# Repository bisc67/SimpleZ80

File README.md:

# SimpleZ80
Very simple Z80 SBC. Why? To figure it out.

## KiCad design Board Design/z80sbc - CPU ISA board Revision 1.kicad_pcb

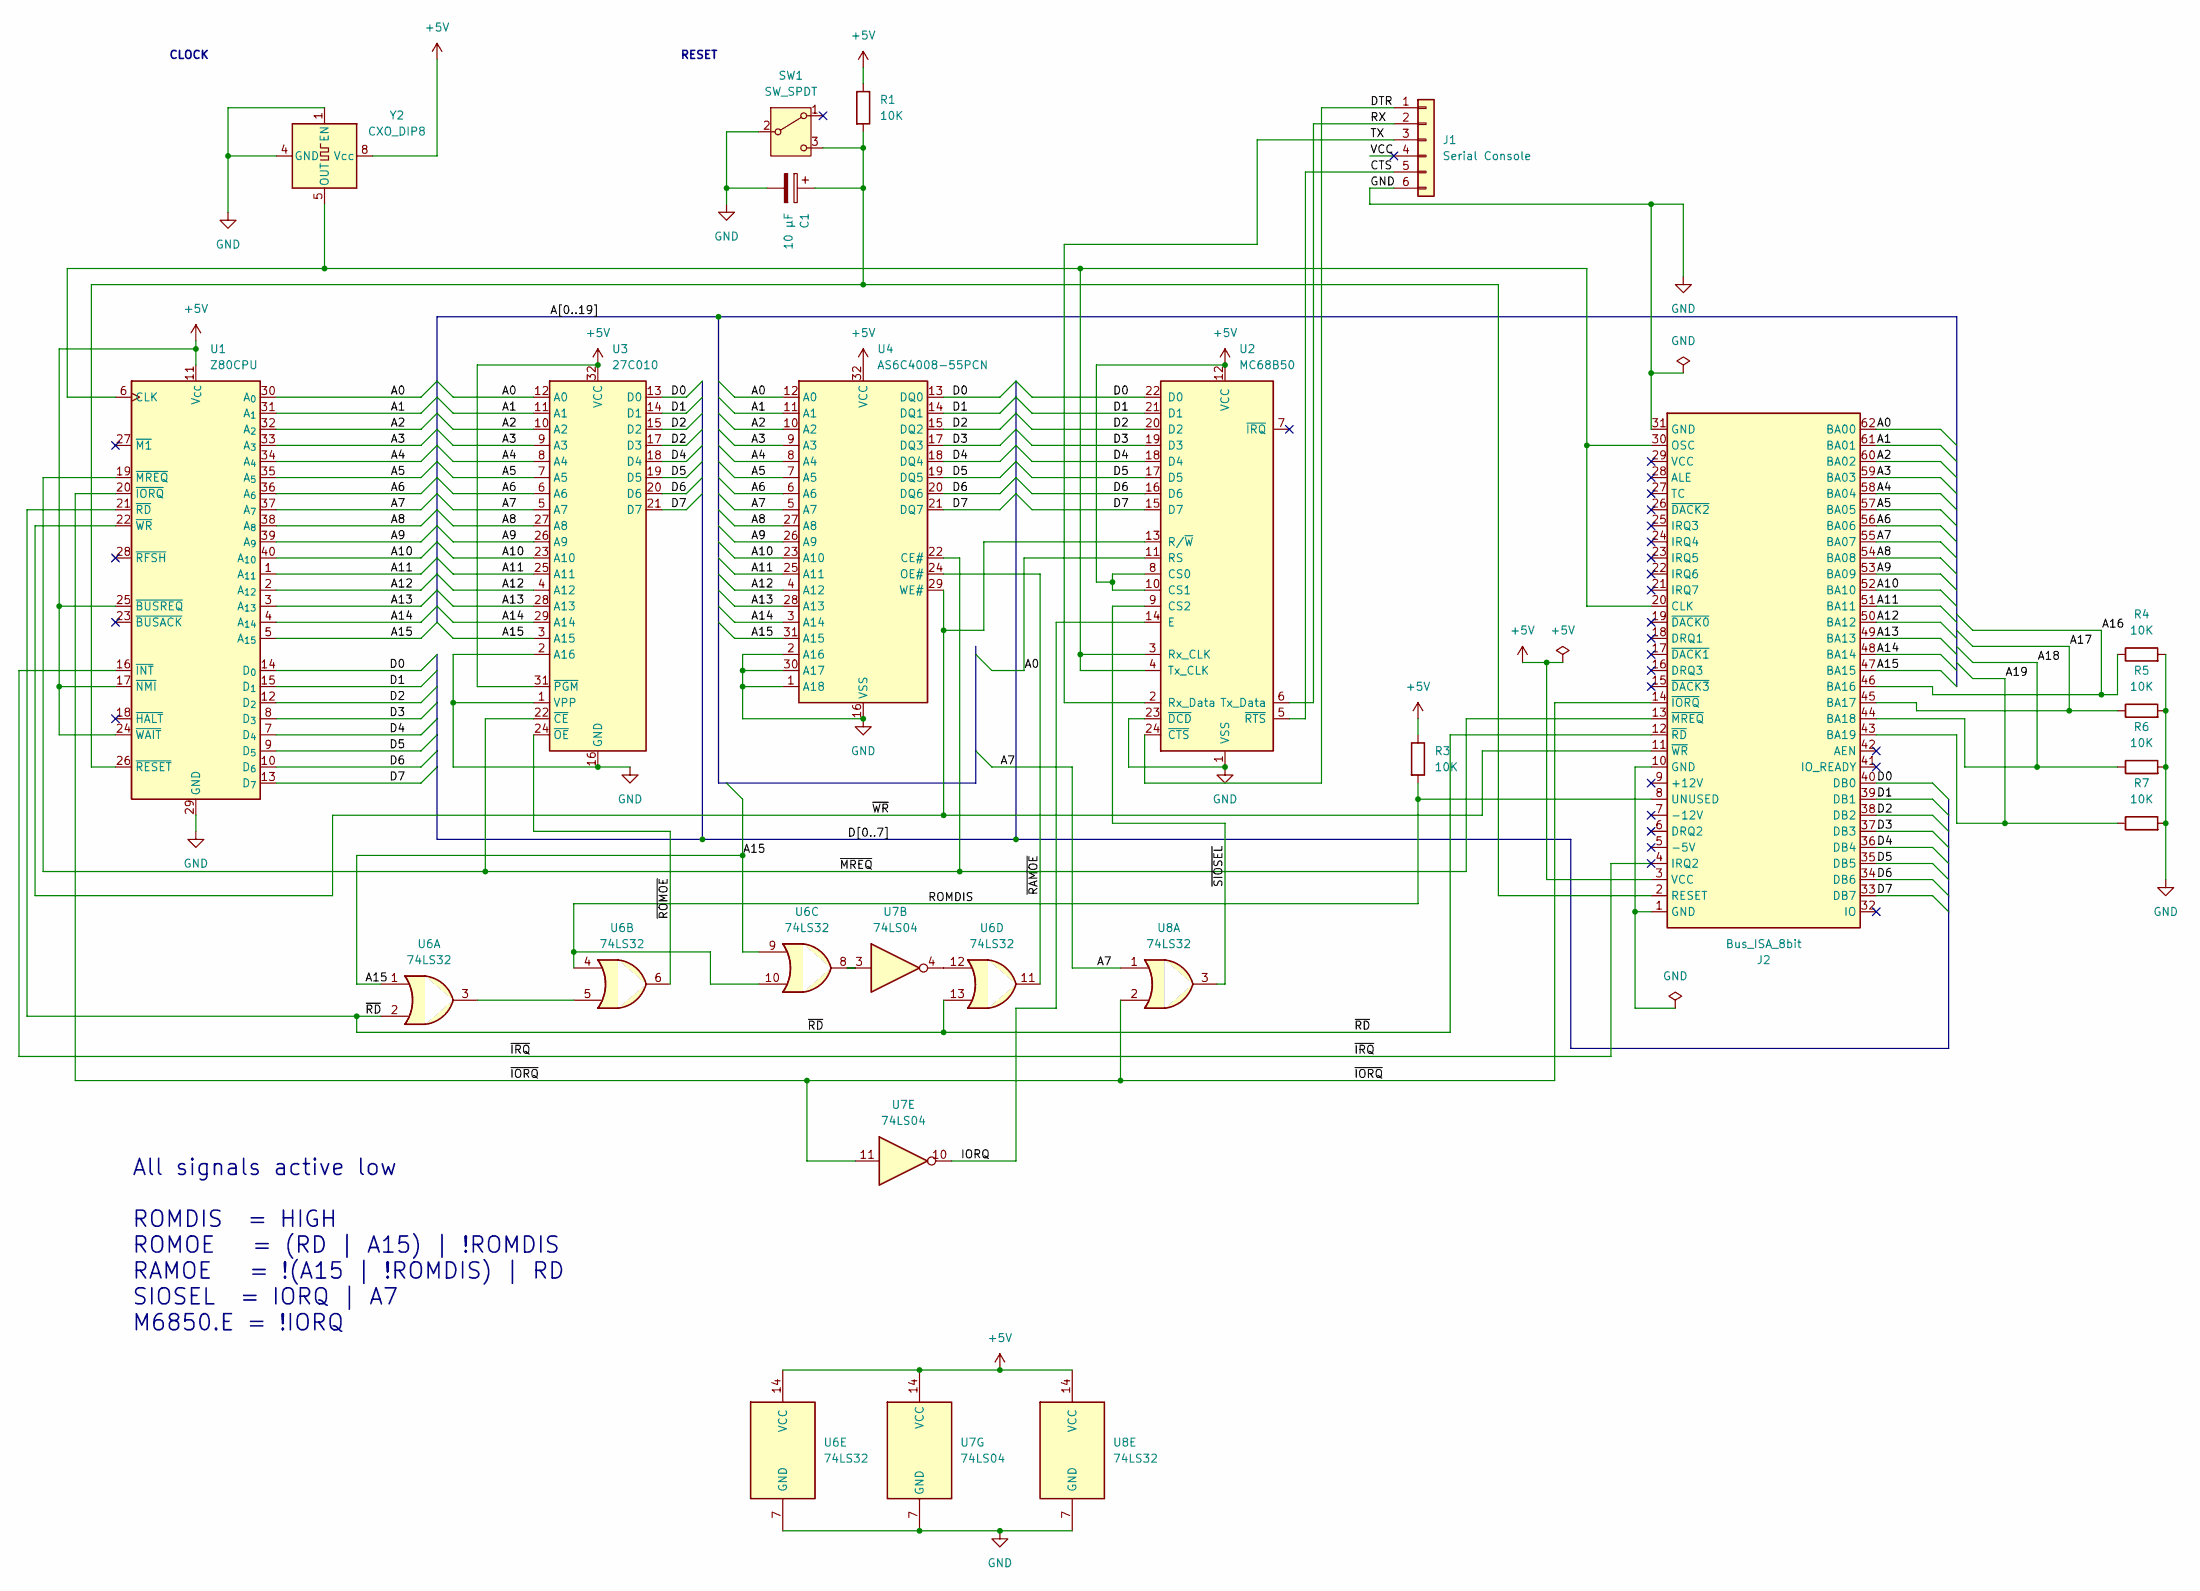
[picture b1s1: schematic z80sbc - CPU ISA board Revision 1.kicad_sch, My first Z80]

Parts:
C1: 10 µF; CP_Radial_D4.0mm_P2.00mm
J1: Serial Console; TerminalBlock_MetzConnect_Type059_RT06306HBWC_1x06_P3.50mm_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
J2: Bus_ISA_8bit; BUS_AT
R1, R3, R4, R5, R6, R7: 10K; R_Axial_DIN0204_L3.6mm_D1.6mm_P5.08mm_Horizontal
SW1: SW_SPDT; SW_Push_1P2T_Vertical_E-Switch_800UDP8P1A1M6
U1: Z80CPU; DIP-40_W15.24mm
U2: MC68B50; DIP-24_W15.24mm
U3: 27C010; DIP-32_W15.24mm
U4: AS6C4008-55PCN; DIP-32_W15.24mm
U6, U8: 74LS32; DIP-14_W7.62mm
U7: 74LS04; DIP-14_W7.62mm
Y2: CXO_DIP8; Oscillator_DIP-8

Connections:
+5V: J2.3 (VCC), R1.1, R3.1, U1.11 (V_{CC}), U1.17 (~NMI), U1.24 (~WAIT), U1.25 (~BUSREQ), U2.8 (CS0), U2.10 (CS1), U2.12 (VCC), U3.31 (~PGM), U3.32 (VCC), U4.32 (VCC), U6.14 (VCC), U7.14 (VCC), U8.14 (VCC), Y2.8 (Vcc)
/A0: J2.62 (BA00), U1.30 (A_{0}), U2.11 (RS), U3.12 (A0), U4.12 (A0)
/A1: J2.61 (BA01), U1.31 (A_{1}), U3.11 (A1), U4.11 (A1)
/A2: J2.60 (BA02), U1.32 (A_{2}), U3.10 (A2), U4.10 (A2)
/A3: J2.59 (BA03), U1.33 (A_{3}), U3.9 (A3), U4.9 (A3)
/A4: J2.58 (BA04), U1.34 (A_{4}), U3.8 (A4), U4.8 (A4)
/A5: J2.57 (BA05), U1.35 (A_{5}), U3.7 (A5), U4.7 (A5)
/A6: J2.56 (BA06), U1.36 (A_{6}), U3.6 (A6), U4.6 (A6)
/A7: J2.55 (BA07), U1.37 (A_{7}), U3.5 (A7), U4.5 (A7), U8.1
/A8: J2.54 (BA08), U1.38 (A_{8}), U3.27 (A8), U4.27 (A8)
/A9: J2.53 (BA09), U1.39 (A_{9}), U3.26 (A9), U4.26 (A9)
/A10: J2.52 (BA10), U1.40 (A_{10}), U3.23 (A10), U4.23 (A10)
/A11: J2.51 (BA11), U1.1 (A_{11}), U3.25 (A11), U4.25 (A11)
/A12: J2.50 (BA12), U1.2 (A_{12}), U3.4 (A12), U4.4 (A12)
/A13: J2.49 (BA13), U1.3 (A_{13}), U3.28 (A13), U4.28 (A13)
/A14: J2.48 (BA14), U1.4 (A_{14}), U3.29 (A14), U4.3 (A14)
/A15: J2.47 (BA15), U1.5 (A_{15}), U3.3 (A15), U4.31 (A15), U6.1, U6.9
/A16: J2.46 (BA16), R4.1
/A17: J2.45 (BA17), R5.1
/A18: J2.44 (BA18), R6.1
/A19: J2.43 (BA19), R7.1
/CTS: J1.5, U2.5 (~RTS)
/D0: J2.40 (DB0), U1.14 (D_{0}), U2.22 (D0), U3.13 (D0), U4.13 (DQ0)
/D1: J2.39 (DB1), U1.15 (D_{1}), U2.21 (D1), U3.14 (D1), U4.14 (DQ1)
/D2: J2.38 (DB2), U1.12 (D_{2}), U2.20 (D2), U3.15 (D2), U3.17 (D3), U4.15 (DQ2)
/D3: J2.37 (DB3), U1.8 (D_{3}), U2.19 (D3), U4.17 (DQ3)
/D4: J2.36 (DB4), U1.7 (D_{4}), U2.18 (D4), U3.18 (D4), U4.18 (DQ4)
/D5: J2.35 (DB5), U1.9 (D_{5}), U2.17 (D5), U3.19 (D5), U4.19 (DQ5)
/D6: J2.34 (DB6), U1.10 (D_{6}), U2.16 (D6), U3.20 (D6), U4.20 (DQ6)
/D7: J2.33 (DB7), U1.13 (D_{7}), U2.15 (D7), U3.21 (D7), U4.21 (DQ7)
/DTR: J1.1, U2.24 (~CTS)
/IORQ: U2.14 (E), U7.10
/RX: J1.2, U2.6 (Tx_Data)
/TX: J1.3, U2.2 (Rx_Data)
/VCC: J1.4
/~IORQ: J2.14 (~IORQ), U1.20 (~IORQ), U7.11, U8.2
/~IRQ: J2.4 (IRQ2), U1.16 (~INT)
/~MREQ: J2.13 (~MREQ), U1.19 (~MREQ), U3.22 (~CE), U4.22 (CE#)
/~RAMOE: U4.24 (OE#), U6.11
/~RD: J2.12 (~RD), U1.21 (~RD), U6.2, U6.13
/~ROMOE: U3.24 (~OE), U6.6
/~SIOSEL: U2.9 (CS2), U8.3
/~WR: J2.11 (~WR), U1.22 (~WR), U2.13 (R/~W), U4.29 (WE#)
GND: C1.2, J1.6, J2.31 (GND), R4.2, R5.2, R6.2, R7.2, SW1.2 (B), U1.29 (GND), U2.1 (VSS), U2.23 (~DCD), U3.1 (VPP), U3.2 (A16), U3.16 (GND), U4.1 (A18), U4.2 (A16), U4.16 (VSS), U4.30 (A17), U6.7 (GND), U7.7 (GND), U8.7 (GND), Y2.1 (EN), Y2.4 (GND)
unnamed: J2.20 (CLK), J2.30 (OSC), U1.6 (CLK), U2.3 (Rx_CLK), U2.4 (Tx_CLK), Y2.5 (OUT)
unnamed: J2.1 (GND), J2.10 (GND)
unnamed: C1.1, J2.2 (RESET), R1.2, SW1.3 (C), U1.26 (~RESET)
unnamed: U6.3, U6.5
unnamed: U6.8, U7.3
unnamed: U6.12, U7.4

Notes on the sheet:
CLOCK
RESET
All signals active low ROMDIS = HIGH ROMOE = (RD | A15) | !ROMDIS RAMOE = !(A15 | !ROMDIS) | RD SIOSEL = IORQ | A7 M6850.E = !IORQ

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
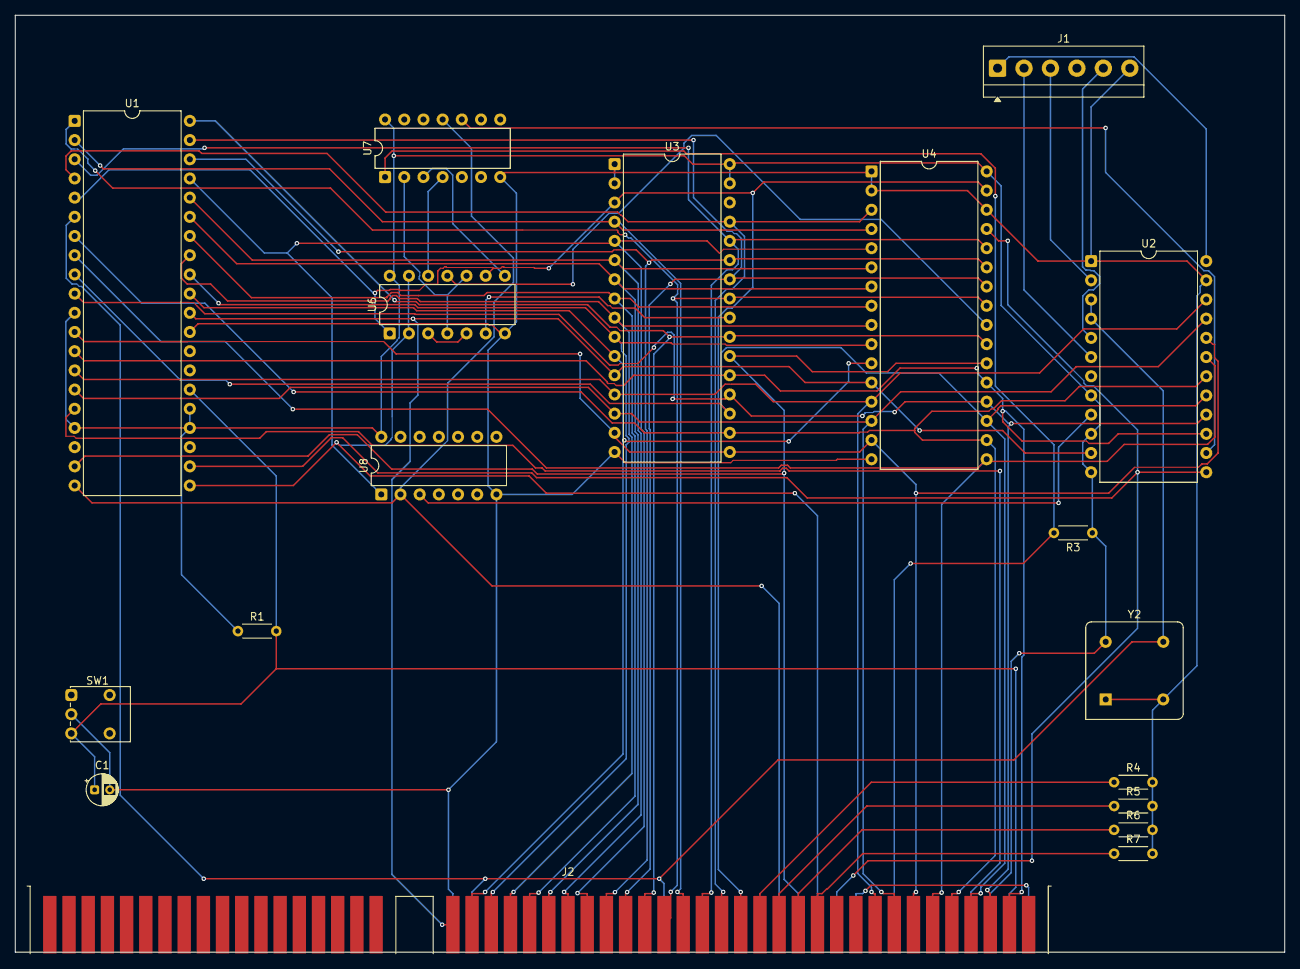
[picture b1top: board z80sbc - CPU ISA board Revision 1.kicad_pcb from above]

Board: 2 copper layers, 168.0 x 124.0 mm, 18 parts (0 on the bottom side), 51 nets.

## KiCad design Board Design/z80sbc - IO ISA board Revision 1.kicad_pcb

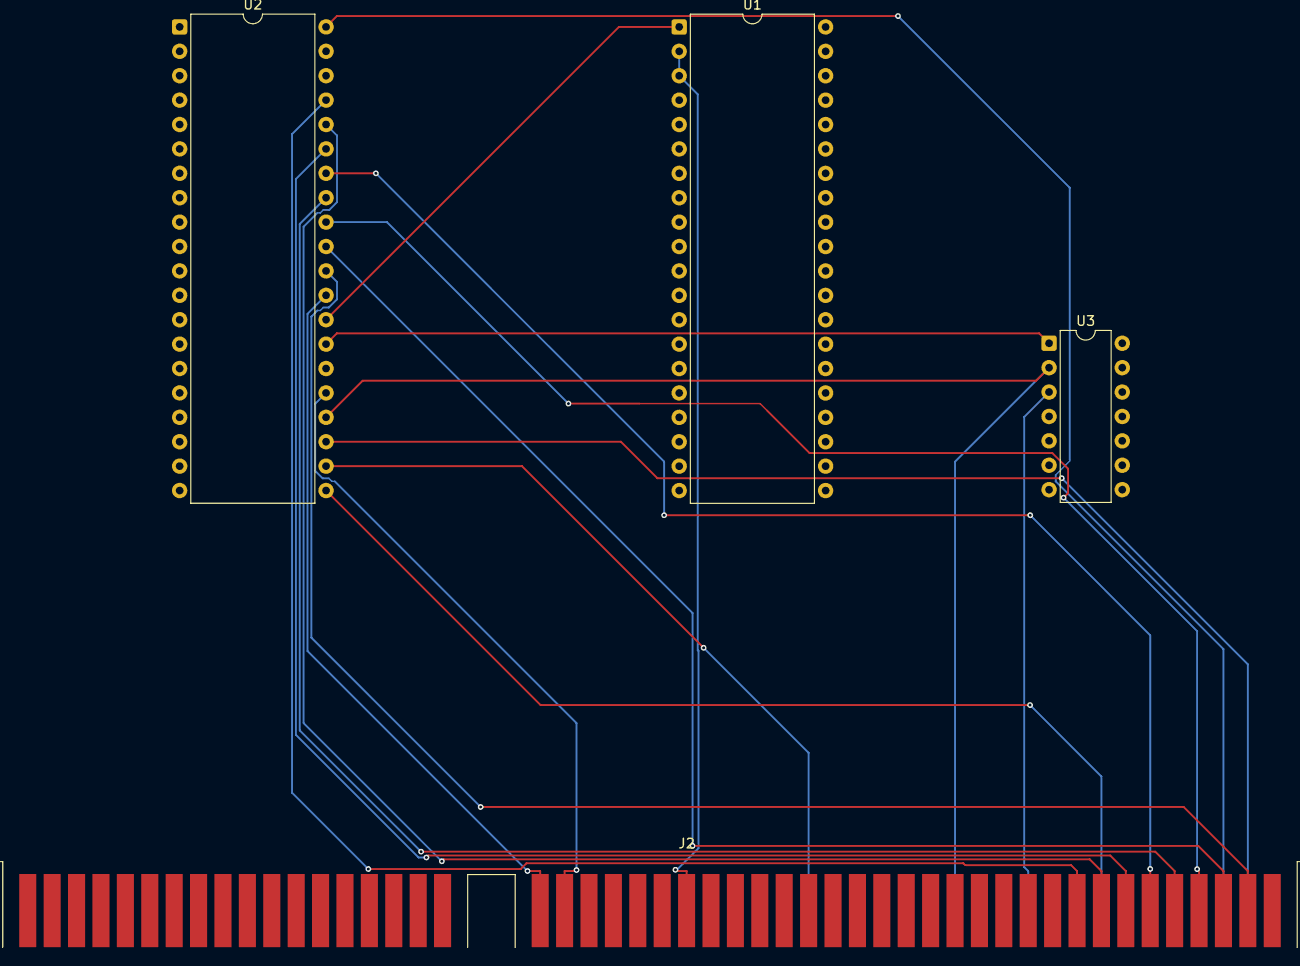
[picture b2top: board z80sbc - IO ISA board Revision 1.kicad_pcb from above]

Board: 2 copper layers, 4 parts (0 on the bottom side), 19 nets.

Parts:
J2: Bus_ISA_8bit; BUS_AT
U1: 74LS02; DIP-40_W15.24mm
U2: AY-3-8910; DIP-40_W15.24mm
U3: 74LS02; DIP-14_W7.62mm

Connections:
+5V: J2.3 (VCC), U2.40 (VCC)
/A0: J2.62 (BA00), U2.29 (BC1)
/A1: J2.61 (BA01), U2.25 (A8)
/A6: J2.56 (BA06), U1.2, U1.3
/D0: J2.40 (DB0), U2.37 (DA0)
/D1: J2.39 (DB1), U2.36 (DA1)
/D2: J2.38 (DB2), U2.35 (DA2)
/D3: J2.37 (DB3), U2.34 (DA3)
/D4: J2.36 (DB4), U2.33 (DA4)
/D5: J2.35 (DB5), U2.32 (DA5)
/D6: J2.34 (DB6), U2.31 (DA6)
/D7: J2.33 (DB7), U2.30 (DA7)
/IORQ: J2.14 (~IORQ), U2.24 (/A9), U3.2
/WR: J2.11 (~WR), U3.3
/~ROMDIS: J2.8 (UNUSED), U2.21 (IOA0)
unnamed: J2.20 (CLK), U2.22 (CLK)
unnamed: J2.2 (RESET), U2.23 (/RESET)
unnamed: U1.1, U2.28 (BC2)
unnamed: U2.27 (BDIR), U3.1

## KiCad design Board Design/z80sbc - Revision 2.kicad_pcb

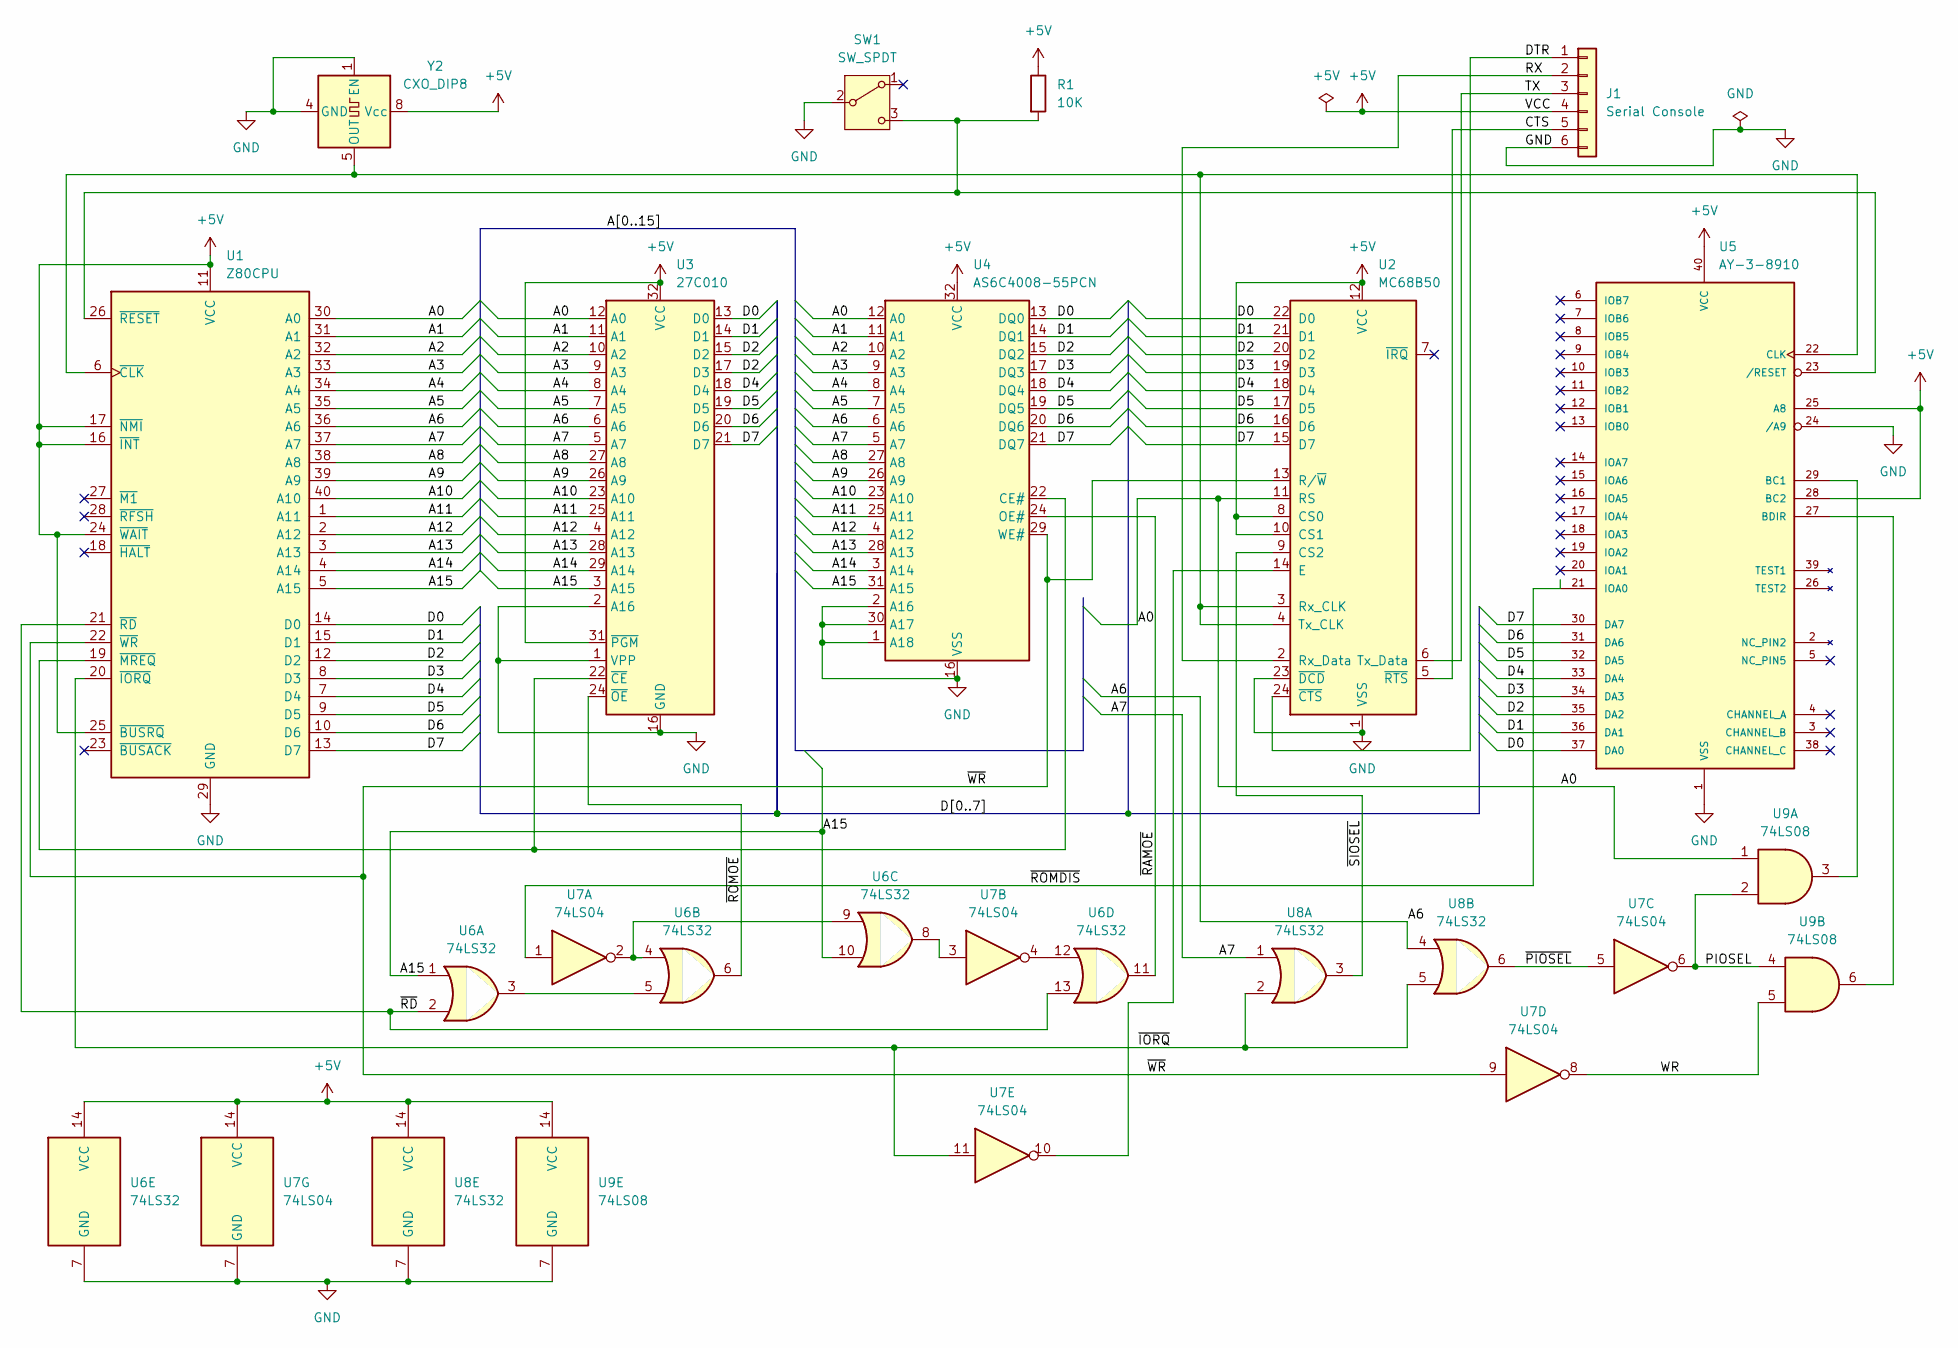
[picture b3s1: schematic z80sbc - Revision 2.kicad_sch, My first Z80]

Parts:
J1: Serial Console; TerminalBlock_MetzConnect_Type059_RT06306HBWC_1x06_P3.50mm_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
R1: 10K; R_Axial_DIN0204_L3.6mm_D1.6mm_P5.08mm_Horizontal
SW1: SW_SPDT; SW_Push_1P2T_Vertical_E-Switch_800UDP8P1A1M6
U1: Z80CPU; DIP-40_W25.4mm_Socket
U2: MC68B50; DIP-24_W15.24mm
U3: 27C010; DIP-32_W15.24mm
U4: AS6C4008-55PCN; DIP-32_W15.24mm
U5: AY-3-8910; DIP-40_W15.24mm
U6, U8: 74LS32; DIP-14_W7.62mm
U7: 74LS04; DIP-14_W7.62mm
U9: 74LS08; DIP-14_W7.62mm
Y2: CXO_DIP8; Oscillator_DIP-8

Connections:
+5V: J1.4, R1.1, U1.7 (D4), U1.8 (D3), U1.9 (D5), U1.10 (D6), U1.11 (VCC), U1.12 (D2), U1.13 (D7), U1.14 (D0), U1.15 (D1), U1.16 (~INT), U1.17 (~NMI), U1.24 (~WAIT), U1.25 (~BUSRQ), U2.8 (CS0), U2.10 (CS1), U2.12 (VCC), U2.15 (D7), U2.16 (D6), U2.17 (D5), U2.18 (D4), U2.19 (D3), U2.20 (D2), U2.21 (D1), U2.22 (D0), U3.13 (D0), U3.14 (D1), U3.15 (D2), U3.17 (D3), U3.18 (D4), U3.19 (D5), U3.20 (D6), U3.21 (D7), U3.31 (~PGM), U3.32 (VCC), U4.13 (DQ0), U4.14 (DQ1), U4.15 (DQ2), U4.17 (DQ3), U4.18 (DQ4), U4.19 (DQ5), U4.20 (DQ6), U4.21 (DQ7), U4.32 (VCC), U5.25 (A8), U5.28 (BC2), U5.30 (DA7), U5.31 (DA6), U5.32 (DA5), U5.33 (DA4), U5.34 (DA3), U5.35 (DA2), U5.36 (DA1), U5.37 (DA0), U5.40 (VCC), U6.14 (VCC), U7.14 (VCC), U8.14 (VCC), U9.14 (VCC), Y2.8 (Vcc)
/A0: U1.30 (A0), U2.11 (RS), U3.12 (A0), U4.12 (A0), U9.1
/A1: U1.31 (A1), U3.11 (A1), U4.11 (A1)
/A2: U1.32 (A2), U3.10 (A2), U4.10 (A2)
/A3: U1.33 (A3), U3.9 (A3), U4.9 (A3)
/A4: U1.34 (A4), U3.8 (A4), U4.8 (A4)
/A5: U1.35 (A5), U3.7 (A5), U4.7 (A5)
/A6: U1.36 (A6), U3.6 (A6), U4.6 (A6), U8.4
/A7: U1.37 (A7), U3.5 (A7), U4.5 (A7), U8.1
/A8: U1.38 (A8), U3.27 (A8), U4.27 (A8)
/A9: U1.39 (A9), U3.26 (A9), U4.26 (A9)
/A10: U1.40 (A10), U3.23 (A10), U4.23 (A10)
/A11: U1.1 (A11), U3.25 (A11), U4.25 (A11)
/A12: U1.2 (A12), U3.4 (A12), U4.4 (A12)
/A13: U1.3 (A13), U3.28 (A13), U4.28 (A13)
/A14: U1.4 (A14), U3.29 (A14), U4.3 (A14)
/A15: U1.5 (A15), U3.3 (A15), U4.31 (A15), U6.1, U6.10
/CTS: J1.5, U2.5 (~RTS)
/DTR: J1.1, U2.24 (~CTS)
/PIOSEL: U7.6, U9.2, U9.4
/RX: J1.2, U2.2 (Rx_Data)
/TX: J1.3, U2.6 (Tx_Data)
/WR: U7.8, U9.5
/~IORQ: U1.20 (~IORQ), U7.11, U8.2, U8.5
/~PIOSEL: U7.5, U8.6
/~RAMOE: U4.24 (OE#), U6.11
/~RD: U1.21 (~RD), U6.2, U6.13
/~ROMDIS: U5.21 (IOA0), U7.1
/~ROMOE: U3.24 (~OE), U6.6
/~SIOSEL: U2.9 (CS2), U8.3
/~WR: U1.22 (~WR), U2.13 (R/~W), U4.29 (WE#), U7.9
GND: J1.6, SW1.2 (B), U1.29 (GND), U2.1 (VSS), U2.23 (~DCD), U3.1 (VPP), U3.2 (A16), U3.16 (GND), U4.1 (A18), U4.2 (A16), U4.16 (VSS), U4.30 (A17), U5.1 (VSS), U5.24 (/A9), U6.7 (GND), U7.7 (GND), U8.7 (GND), U9.7 (GND), Y2.1 (EN), Y2.4 (GND)
unnamed: R1.2, SW1.3 (C), U1.26 (~RESET), U5.23 (/RESET)
unnamed: U1.6 (~CLK), U2.3 (Rx_CLK), U2.4 (Tx_CLK), U5.22 (CLK), Y2.5 (OUT)
unnamed: U1.19 (~MREQ), U3.22 (~CE), U4.22 (CE#)
unnamed: U2.14 (E), U7.10
unnamed: U5.29 (BC1), U9.3
unnamed: U5.27 (BDIR), U9.6
unnamed: U6.3, U6.5
unnamed: U6.4, U6.9, U7.2
unnamed: U6.8, U7.3
unnamed: U6.12, U7.4

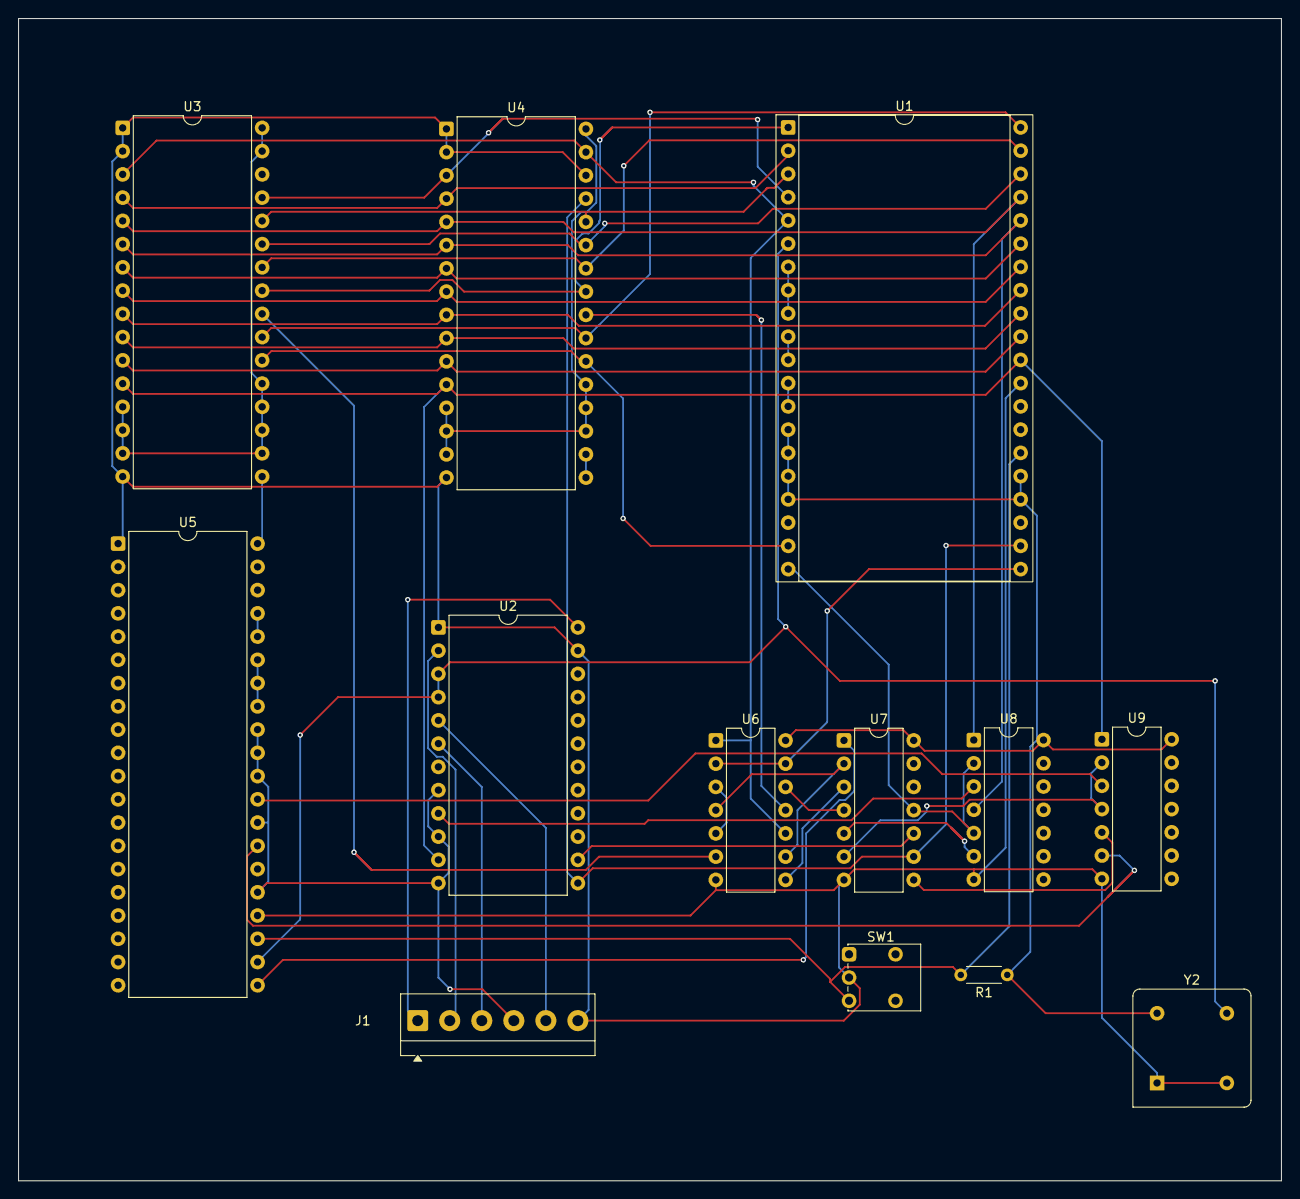
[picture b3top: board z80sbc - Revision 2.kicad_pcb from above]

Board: 2 copper layers, 138.0 x 127.0 mm, 13 parts (0 on the bottom side), 42 nets.

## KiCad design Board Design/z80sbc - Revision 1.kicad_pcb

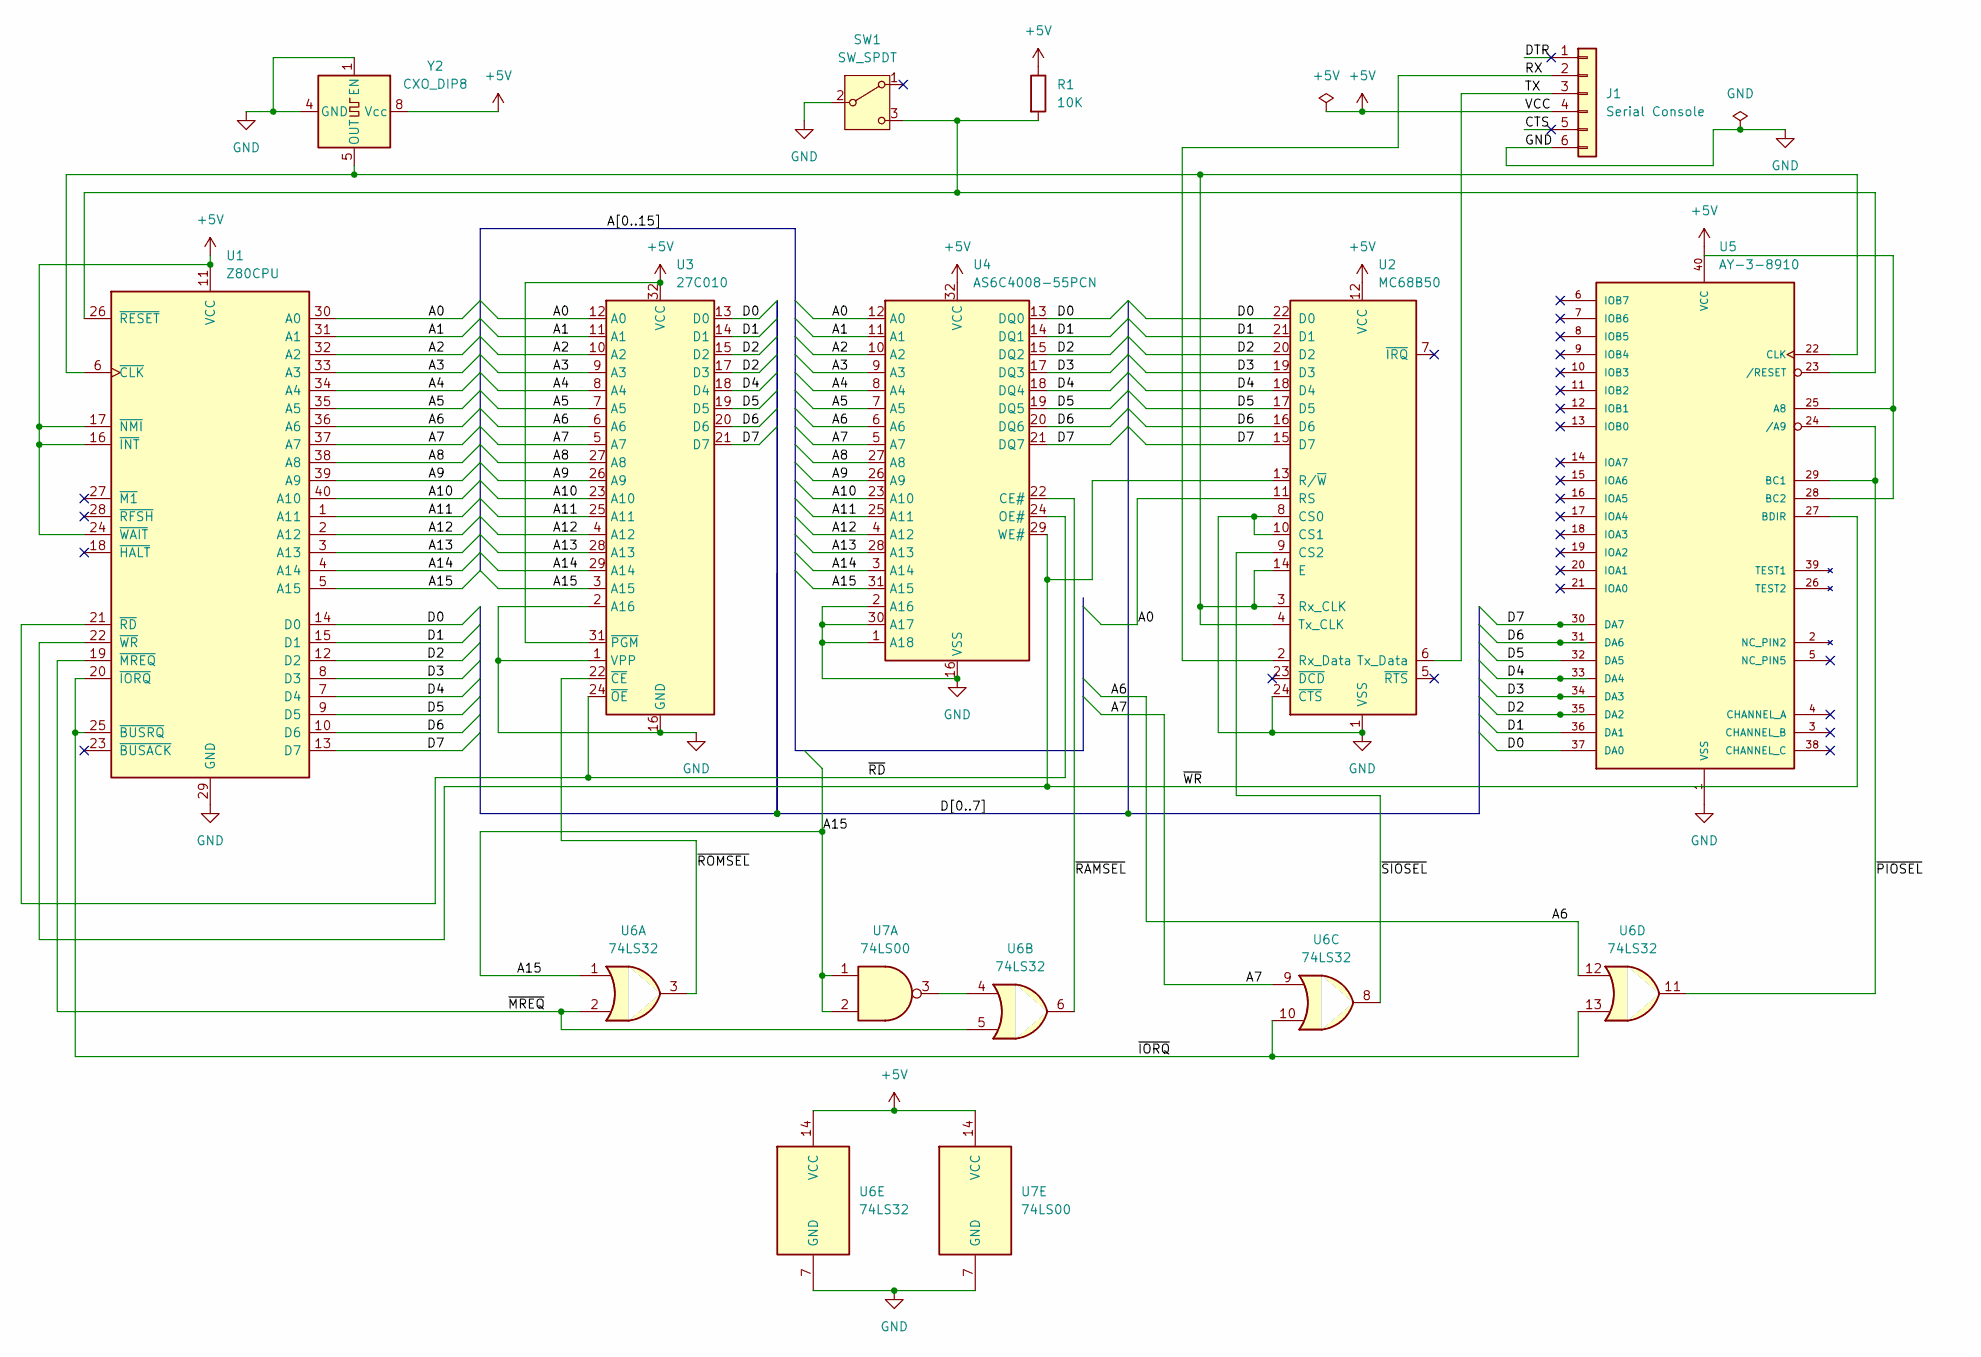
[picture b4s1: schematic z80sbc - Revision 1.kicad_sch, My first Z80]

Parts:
J1: Serial Console; TerminalBlock_MetzConnect_Type059_RT06306HBWC_1x06_P3.50mm_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
R1: 10K; R_Axial_DIN0204_L3.6mm_D1.6mm_P5.08mm_Horizontal
SW1: SW_SPDT; SW_Push_1P2T_Vertical_E-Switch_800UDP8P1A1M6
U1: Z80CPU; DIP-40_W25.4mm_Socket
U2: MC68B50; DIP-24_W15.24mm
U3: 27C010; DIP-32_W15.24mm
U4: AS6C4008-55PCN; DIP-32_W15.24mm
U5: AY-3-8910; DIP-40_W15.24mm
U6: 74LS32; DIP-14_W7.62mm
U7: 74LS00; DIP-14_W7.62mm
Y2: CXO_DIP8; Oscillator_DIP-8

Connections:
+5V: J1.4, R1.1, U1.11 (VCC), U1.16 (~INT), U1.17 (~NMI), U1.24 (~WAIT), U2.12 (VCC), U3.31 (~PGM), U3.32 (VCC), U4.32 (VCC), U5.40 (VCC), U6.14 (VCC), U7.14 (VCC), Y2.8 (Vcc)
/A0: U1.30 (A0), U2.11 (RS), U3.12 (A0), U4.12 (A0)
/A1: U1.31 (A1), U3.11 (A1), U4.11 (A1)
/A2: U1.32 (A2), U3.10 (A2), U4.10 (A2)
/A3: U1.33 (A3), U3.9 (A3), U4.9 (A3)
/A4: U1.34 (A4), U3.8 (A4), U4.8 (A4)
/A5: U1.35 (A5), U3.7 (A5), U4.7 (A5)
/A6: U1.36 (A6), U3.6 (A6), U4.6 (A6), U6.12
/A7: U1.37 (A7), U3.5 (A7), U4.5 (A7), U6.9
/A8: U1.38 (A8), U3.27 (A8), U4.27 (A8)
/A9: U1.39 (A9), U3.26 (A9), U4.26 (A9)
/A10: U1.40 (A10), U3.23 (A10), U4.23 (A10)
/A11: U1.1 (A11), U3.25 (A11), U4.25 (A11)
/A12: U1.2 (A12), U3.4 (A12), U4.4 (A12)
/A13: U1.3 (A13), U3.28 (A13), U4.28 (A13)
/A14: U1.4 (A14), U3.29 (A14), U4.3 (A14)
/A15: U1.5 (A15), U3.3 (A15), U4.31 (A15), U6.1, U7.1, U7.2
/CTS: J1.5
/D0: U1.14 (D0), U2.22 (D0), U3.13 (D0), U4.13 (DQ0), U5.37 (DA0)
/D1: U1.15 (D1), U2.21 (D1), U3.14 (D1), U4.14 (DQ1), U5.36 (DA1)
/D2: U1.12 (D2), U2.20 (D2), U3.15 (D2), U3.17 (D3), U4.15 (DQ2), U5.35 (DA2)
/D3: U1.8 (D3), U2.19 (D3), U4.17 (DQ3), U5.34 (DA3)
/D4: U1.7 (D4), U2.18 (D4), U3.18 (D4), U4.18 (DQ4), U5.33 (DA4)
/D5: U1.9 (D5), U2.17 (D5), U3.19 (D5), U4.19 (DQ5), U5.32 (DA5)
/D6: U1.10 (D6), U2.16 (D6), U3.20 (D6), U4.20 (DQ6), U5.31 (DA6)
/D7: U1.13 (D7), U2.15 (D7), U3.21 (D7), U4.21 (DQ7), U5.30 (DA7)
/DTR: J1.1
/RX: J1.2, U2.2 (Rx_Data)
/TX: J1.3, U2.6 (Tx_Data)
/~IORQ: U1.20 (~IORQ), U1.25 (~BUSRQ), U6.10, U6.13
/~MREQ: U1.19 (~MREQ), U6.2, U6.5
/~PIOSEL: U5.24 (/A9), U5.29 (BC1), U6.11
/~RAMSEL: U4.22 (CE#), U6.6
/~RD: U1.21 (~RD), U3.24 (~OE), U4.24 (OE#)
/~ROMSEL: U3.22 (~CE), U6.3
/~SIOSEL: U2.9 (CS2), U6.8
/~WR: U1.22 (~WR), U2.13 (R/~W), U4.29 (WE#), U5.27 (BDIR)
GND: J1.6, SW1.2 (B), U1.29 (GND), U2.1 (VSS), U2.8 (CS0), U2.10 (CS1), U2.24 (~CTS), U3.1 (VPP), U3.2 (A16), U3.16 (GND), U4.1 (A18), U4.2 (A16), U4.16 (VSS), U4.30 (A17), U5.1 (VSS), U6.7 (GND), U7.7 (GND), Y2.1 (EN), Y2.4 (GND)
unnamed: R1.2, SW1.3 (C), U1.26 (~RESET), U5.23 (/RESET)
unnamed: U1.6 (~CLK), U2.3 (Rx_CLK), U2.4 (Tx_CLK), U2.14 (E), U5.22 (CLK), Y2.5 (OUT)
unnamed: U5.25 (A8), U5.28 (BC2)
unnamed: U6.4, U7.3

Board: 2 copper layers, 11 parts (0 on the bottom side), 40 nets, no tracks yet.

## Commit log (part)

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2025-07-02 Initial code checkin
2025-07-10 Working up to 28,800. Now contains bit rate toggle, ROM paging and some initial support for interrupt driven I/O. PCB updated with new wiring, E signal for AY-3-8910 now derived from !IORQ.
2025-07-14 Added display initialization.
